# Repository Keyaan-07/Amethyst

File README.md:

# Amethyst
Amethyst is an 84-key keyboard with a small form factor. It comes with the RP2040 and i have used purple akko v3 switches to give it purple colour. This keyboard runs qmk firmware and can be found under firmware. The complete design file is amethyst.step.

# Soldering and setup
1. Order the PCB from the gerbers present in hardware/production. 
2. order the parts from the given links in bom.csv file
3. first solder the smd components on the back side and then proceed to the through hole keys. 
4. press the heated inserts in the case with the help of a soldering iron. 
5. screw in the case. 
6. fit the keycaps on the top. 
7. short the BOOT and GND pads with a screwdriver and plug in the usb cable.
8. go to the firmware folder and download the .uf2 file. 
9. drag and drop the .uf2 file to the "RPI-RP2" drive that just popped up.
10. Your keyboard is now ready!!

## Why I made this keyboard
 I am getting a new laptop this year and did not want to let go of the keymap of the old keyboard, thus I created amethyst. 

# BOM
|Designator                                                                                                                                                                                                                                                                                                                                                                                                               |Function                      |Value                      |Footprint                            |Quantity|Price   |Amount |Order|Link                                                                                                                                     |
|-------------------------------------------------------------------------------------------------------------------------------------------------------------------------------------------------------------------------------------------------------------------------------------------------------------------------------------------------------------------------------------------------------------------------|------------------------------|---------------------------|-------------------------------------|--------|--------|-------|-----|-----------------------------------------------------------------------------------------------------------------------------------------|
|PCB                                                                                                                                                                                                                                                                                                                                                                                                                      |Main PCB                      |                           |119x312                              |5       |8.934   |44.67  |Yes  |https://robu.in/product/online-pcb-manufacturing-service/                                                                                |
|Keycaps                                                                                                                                                                                                                                                                                                                                                                                                                  |Purple keycaps                |                           |                                     |1       |11.48   |11.48  |Yes  |https://curiositycaps.in/products/macarons-cherry-pbt-keycaps?_pos=368&_fid=c796727f4&_ss=c                                              |
|Keys                                                                                                                                                                                                                                                                                                                                                                                                                     |Akko v3 lavender(pack of 45)  |                           |                                     |2       |11.48   |22.96  |Yes  |https://stackskb.com/store/akko-v3-lavender-purple-pro-switch-pack-of-45/                                                                |
|Stabilizers                                                                                                                                                                                                                                                                                                                                                                                                              |Clear                         |                           |                                     |1       |11.67   |11.67  |Yes  |https://stackskb.com/store/durock-clear-screw-in-stabilizers-v2/?attribute_combination=4%2B1+Set&attribute_spacebar-size=6.25U           |
|Case                                                                                                                                                                                                                                                                                                                                                                                                                     |print legion                  |                           |                                     |1       |0       |0      |Yes  |https://printlegion.hackclub.com/                                                                                                        |
|C1, C2                                                                                                                                                                                                                                                                                                                                                                                                                   |Capacitor                     |15p                        |402                                  |2       |0.017   |0.034  |Yes  |https://robu.in/product/gjm1555c1h150gb01d-murata-electronics-50v-15pf-null-%c2%b12-0402-multilayer-ceramic-capacitors-mlcc-smd-smt-rohs/|
|C13, C22                                                                                                                                                                                                                                                                                                                                                                                                                 |Capacitor                     |10u                        |805                                  |2       |0.05    |0.1    |No   |https://www.lcsc.com/product-detail/C2932476.html                                                                                        |
|C14, C15, C16, C17, C18, C19, C20, C23, C24, C25                                                                                                                                                                                                                                                                                                                                                                         |Capacitor                     |100n                       |402                                  |10      |0.0074  |0.074  |No   |https://www.lcsc.com/product-detail/C426067.html                                                                                         |
|C4, C5, C6                                                                                                                                                                                                                                                                                                                                                                                                               |Capacitor                     |1u                         |402                                  |3       |0.02    |0.06   |No   |https://www.lcsc.com/product-detail/C1518208.html                                                                                        |
|D1, D10, D11, D12, D13, D14, D15, D16, D17, D18, D19, D2, D20, D21, D22, D23, D24, D25, D26, D27, D28, D29, D3, D30, D31, D32, D33, D34, D35, D36, D37, D38, D39, D4, D40, D41, D42, D43, D44, D45, D46, D47, D48, D49, D5, D50, D51, D52, D53, D54, D55, D56, D57, D58, D59, D6, D60, D61, D62, D63, D64, D65, D66, D67, D68, D69, D7, D70, D71, D72, D73, D74, D75, D76, D77, D78, D79, D8, D80, D81, D82, D83, D84, D9|Diodes                        |1N4148W                    |D_SOD-123                            |90      |0.0073  |0.657  |Yes  |https://robu.in/product/1n4148w-sod-123-1206-diodereel-of-3000/                                                                          |
|J2                                                                                                                                                                                                                                                                                                                                                                                                                       |USB-C                         |USB_C_Receptacle_USB2.0_16P|USB_C_Receptacle_XKB_U262-16XN-4BVC11|1       |0.06    |0.06   |No   |https://www.lcsc.com/product-detail/C393939.html                                                                                         |
|R1, R2                                                                                                                                                                                                                                                                                                                                                                                                                   |Resistors                     |5.1k                       |402                                  |2       |0.005   |0.01   |No   |https://www.lcsc.com/product-detail/C278598.html                                                                                         |
|R3, R6                                                                                                                                                                                                                                                                                                                                                                                                                   |Resistors                     |1k                         |402                                  |2       |0.02    |0.04   |No   |https://www.lcsc.com/product-detail/C427241.html                                                                                         |
|R4, R5                                                                                                                                                                                                                                                                                                                                                                                                                   |Resistors                     |27                         |402                                  |2       |0.0039  |0.0078 |No   |https://www.lcsc.com/product-detail/C278580.html                                                                                         |
|U1                                                                                                                                                                                                                                                                                                                                                                                                                       |MCU                           |RP2040                     |QFN-56-1EP_7x7mm_P0.4mm_EP3.2x3.2mm  |2       |0.89    |1.78   |Yes  |https://robu.in/product/raspberry-pi-rp2040/                                                                                             |
|U2                                                                                                                                                                                                                                                                                                                                                                                                                       |Flash                         |W25Q128JVS                 |SOIC-8_5.3x5.3mm_P1.27mm             |1       |1.1     |1.1    |No   |https://www.lcsc.com/product-detail/C2613930.html                                                                                        |
|U3                                                                                                                                                                                                                                                                                                                                                                                                                       |Regulator                     |AMS1117-3.3                |SOT-89-3                             |1       |0.1     |0.1    |No   |https://www.lcsc.com/product-detail/C917152.html                                                                                         |
|Y1                                                                                                                                                                                                                                                                                                                                                                                                                       |Crystal Oscillator            |Crystal_GND24              |Crystal_SMD_3225-4Pin_3.2x2.5mm      |1       |0.38    |0.38   |No   |https://www.lcsc.com/product-detail/C20625731.html                                                                                       |
|                                                                                                                                                                                                                                                                                                                                                                                                                         |                              |                           |                                     |        |Shipping|0.51   |     |                                                                                                                                         |
|                                                                                                                                                                                                                                                                                                                                                                                                                         |                              |                           |                                     |        |Total   |100.693|     |                                                                                                                                         |

# 3d Files link
All the 3d files can be found on onshape [here](https://cad.onshape.com/documents/0f11901139fd6ce9006e5c5f/w/93aac7747a7c2381c6948375/e/141b0f824d8e79d984ecb6aa?renderMode=0&uiState=6a158fa1dd36a79bc530a0cf)

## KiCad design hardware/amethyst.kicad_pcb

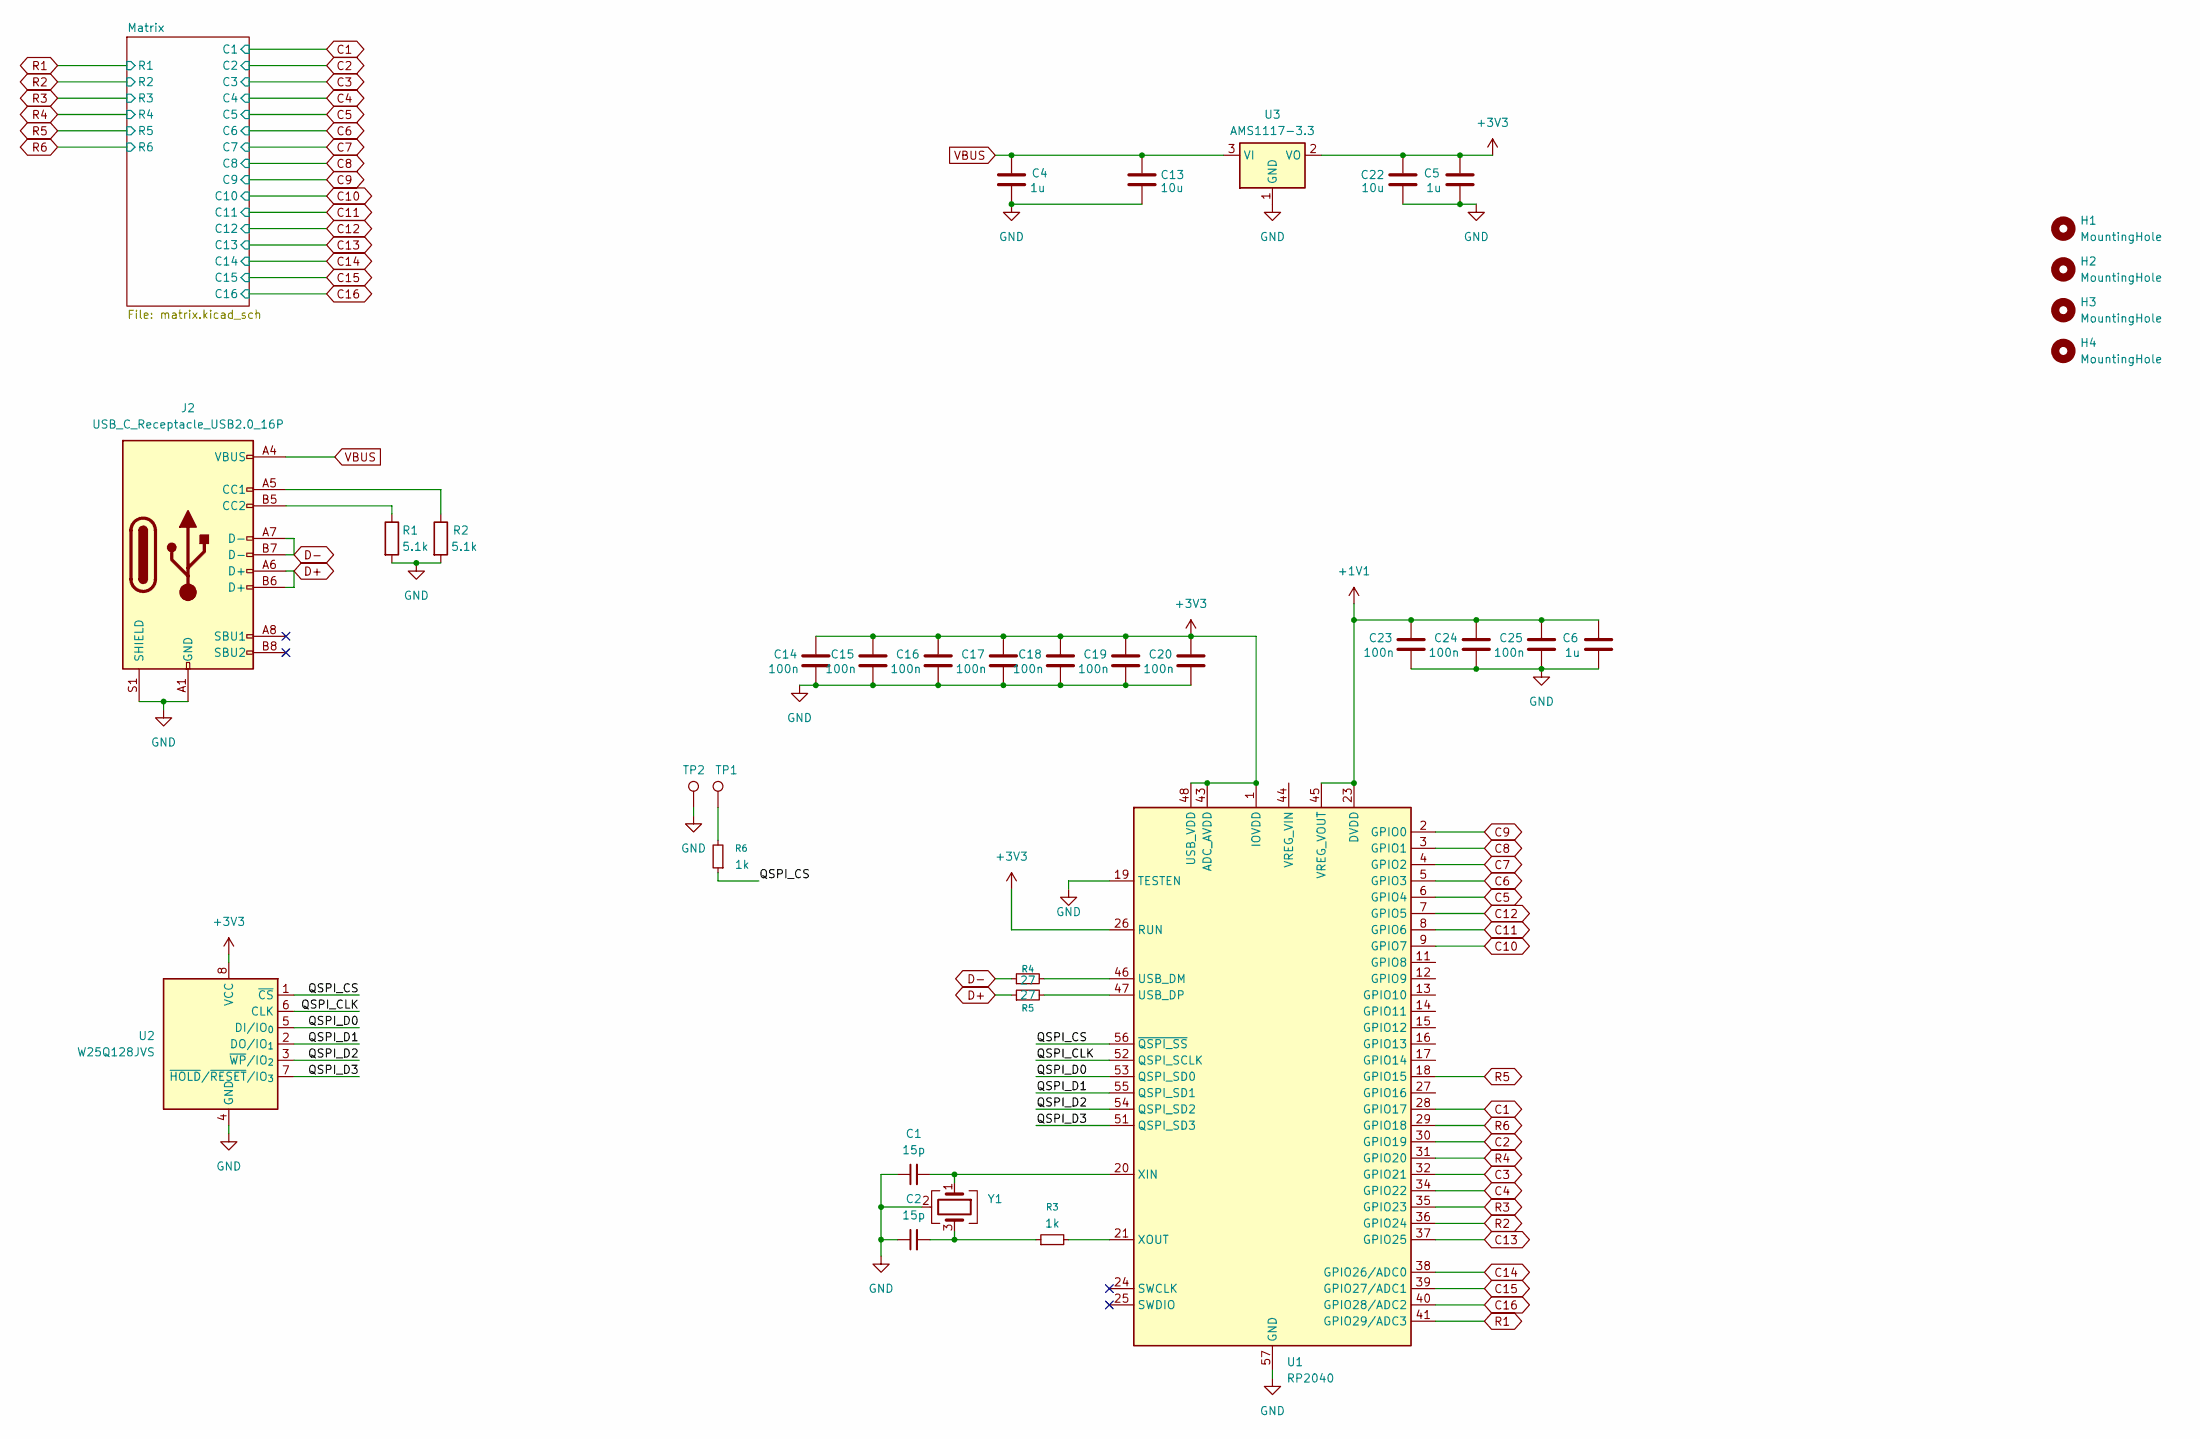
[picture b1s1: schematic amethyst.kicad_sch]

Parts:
C1, C2: 15p; C_0402_1005Metric
C4, C5, C6: 1u; C_0402_1005Metric
C13, C22: 10u; C_0805_2012Metric
C14, C15, C16, C17, C18, C19, C20, C23, C24, C25: 100n; C_0402_1005Metric
H1, H2, H3, H4: MountingHole; MountingHole_3.2mm_M3
J2: USB_C_Receptacle_USB2.0_16P; USB_C_Receptacle_XKB_U262-16XN-4BVC11
R1, R2: 5.1k; R_0402_1005Metric
R3, R6: 1k; R_0402_1005Metric
R4, R5: 27; R_0402_1005Metric
TP1, TP2: TestPoint; TestPoint_Pad_1.0x1.0mm
U1: RP2040; QFN-56-1EP_7x7mm_P0.4mm_EP3.2x3.2mm
U2: W25Q128JVS; SOIC-8_5.3x5.3mm_P1.27mm
U3: AMS1117-3.3; SOT-89-3
Y1: Crystal_GND24; Crystal_SMD_3225-4Pin_3.2x2.5mm

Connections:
+1V1: C6.2, C23.2, C24.2, C25.2, U1.23 (DVDD), U1.45 (VREG_VOUT), U1.50 (DVDD)
+3V3: C5.2, C14.2, C15.2, C16.2, C17.2, C18.2, C19.2, C20.2, C22.1, U1.1 (IOVDD), U1.10 (IOVDD), U1.22 (IOVDD), U1.26 (RUN), U1.33 (IOVDD), U1.42 (IOVDD), U1.43 (ADC_AVDD), U1.48 (USB_VDD), U1.49 (IOVDD), U2.8 (VCC), U3.2 (VO)
/QSPI_CLK: U1.52 (QSPI_SCLK), U2.6 (CLK)
/QSPI_CS: R6.1, U1.56 (~QSPI_SS), U2.1 (~CS)
/QSPI_D0: U1.53 (QSPI_SD0), U2.5 (DI/IO_{0})
/QSPI_D1: U1.55 (QSPI_SD1), U2.2 (DO/IO_{1})
/QSPI_D2: U1.54 (QSPI_SD2), U2.3 (~WP/IO_{2})
/QSPI_D3: U1.51 (QSPI_SD3), U2.7 (~HOLD/~RESET/IO_{3})
C1: U1.28 (GPIO17); also elsewhere on the board
C2: U1.30 (GPIO19); also elsewhere on the board
C3: U1.32 (GPIO21); also elsewhere on the board
C4: U1.34 (GPIO22); also elsewhere on the board
C5: U1.6 (GPIO4); also elsewhere on the board
C6: U1.5 (GPIO3); also elsewhere on the board
C7: U1.4 (GPIO2); also elsewhere on the board
C8: U1.3 (GPIO1); also elsewhere on the board
C9: U1.2 (GPIO0); also elsewhere on the board
C10: U1.9 (GPIO7); also elsewhere on the board
C11: U1.8 (GPIO6); also elsewhere on the board
C12: U1.7 (GPIO5); also elsewhere on the board
C13: U1.37 (GPIO25); also elsewhere on the board
C14: U1.38 (GPIO26/ADC0); also elsewhere on the board
C15: U1.39 (GPIO27/ADC1); also elsewhere on the board
C16: U1.40 (GPIO28/ADC2); also elsewhere on the board
D+: J2.A6 (D+), J2.B6 (D+), R5.1
D-: J2.A7 (D-), J2.B7 (D-), R4.1
GND: C1.1, C2.1, C4.1, C5.1, C6.1, C13.2, C14.1, C15.1, C16.1, C17.1, C18.1, C19.1, C20.1, C22.2, C23.1, C24.1, C25.1, J2.A1 (GND), J2.A12 (GND), J2.B1 (GND), J2.B12 (GND), J2.S1 (SHIELD), R1.2, R2.2, TP2.1 (1_1), U1.19 (TESTEN), U1.57 (GND), U2.4 (GND), U3.1 (GND), Y1.2 (G), Y1.4 (G)
unnamed: C2.2, R3.1, Y1.3
unnamed: J2.A5 (CC1), R2.1
unnamed: J2.B5 (CC2), R1.1
unnamed: R6.2, TP1.1 (1_1)
unnamed: R4.2, U1.46 (USB_DM)
unnamed: R5.2, U1.47 (USB_DP)
unnamed: C1.2, U1.20 (XIN), Y1.1
unnamed: R3.2, U1.21 (XOUT)
R1: U1.41 (GPIO29/ADC3); also elsewhere on the board
R2: U1.36 (GPIO24); also elsewhere on the board
R3: U1.35 (GPIO23); also elsewhere on the board
R4: U1.31 (GPIO20); also elsewhere on the board
R5: U1.18 (GPIO15); also elsewhere on the board
R6: U1.29 (GPIO18); also elsewhere on the board
VBUS: C4.2, C13.1, J2.A4 (VBUS), J2.A9 (VBUS), J2.B4 (VBUS), J2.B9 (VBUS), U3.3 (VI)

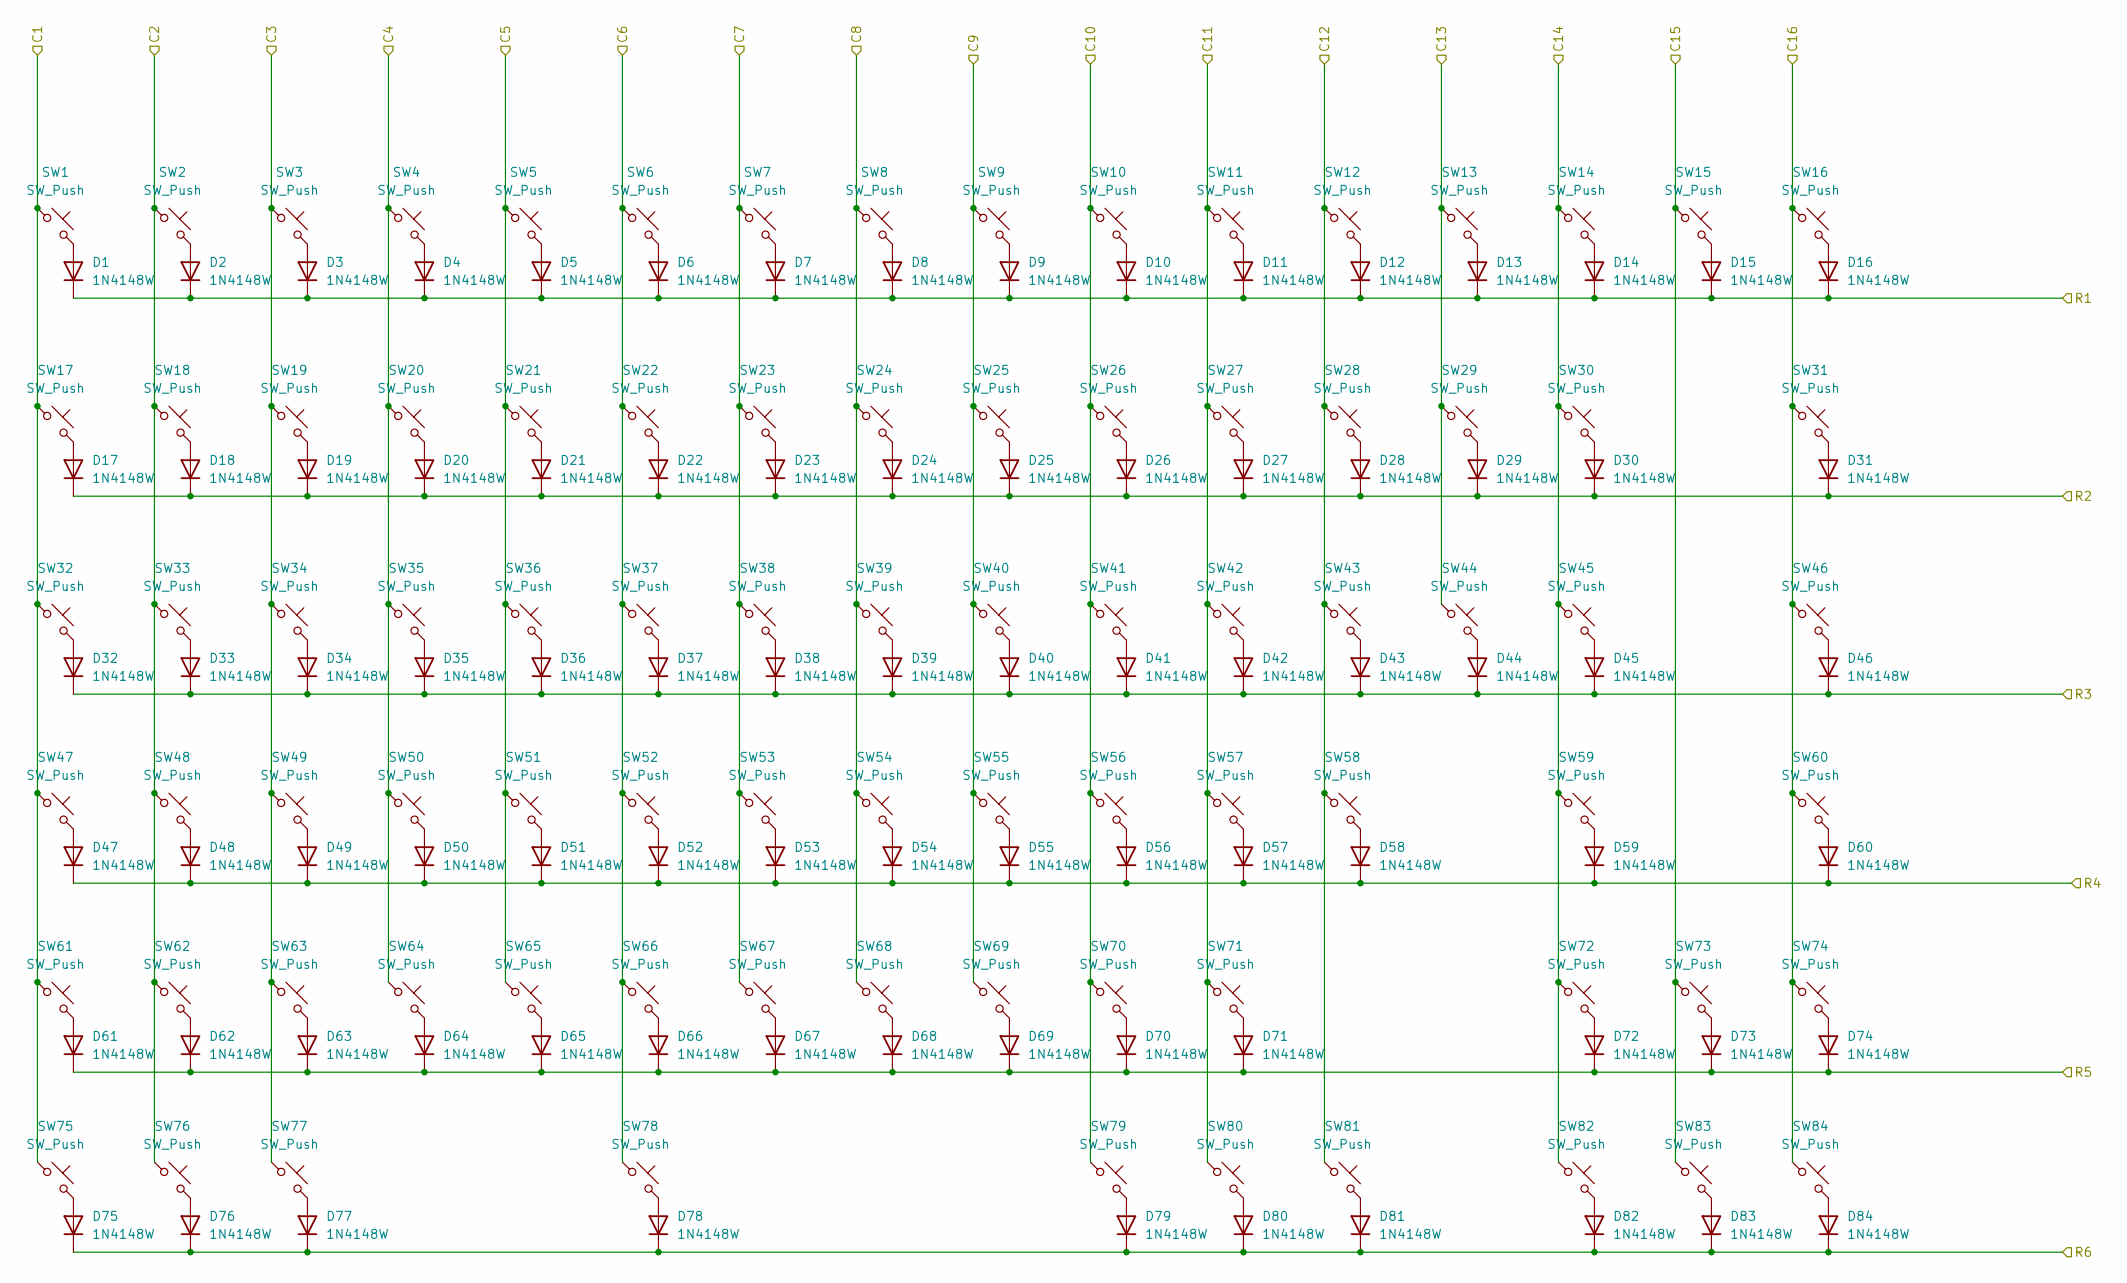
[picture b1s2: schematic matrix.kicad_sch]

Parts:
D1, D2, D3, D4, D5, D6, D7, D8, D9, D10, D11, D12, D13, D14, D15, D16, D17, D18, D19, D20, D21, D22, D23, D24, D25, D26, D27, D28, D29, D30, D31, D32, D33, D34, D35, D36, D37, D38, D39, D40, D41, D42, D43, D44, D45, D46, D47, D48, D49, D50, D51, D52, D53, D54, D55, D56, D57, D58, D59, D60, D61, D62, D63, D64, D65, D66, D67, D68, D69, D70, D71, D72, D73, D74, D75, D76, D77, D78, D79, D80, D81, D82, D83, D84: 1N4148W; D_SOD-123
SW1, SW2, SW3, SW4, SW5, SW6, SW7, SW8, SW9, SW10, SW11, SW12, SW13, SW14, SW15, SW16, SW17, SW18, SW19, SW20, SW21, SW22, SW23, SW24, SW25, SW26, SW27, SW28, SW29, SW31, SW33, SW34, SW35, SW36, SW37, SW38, SW39, SW40, SW41, SW42, SW43, SW44, SW46, SW48, SW49, SW50, SW51, SW52, SW53, SW54, SW55, SW56, SW57, SW58, SW60, SW62, SW63, SW64, SW65, SW66, SW67, SW68, SW69, SW70, SW71, SW73, SW74, SW79, SW80, SW81, SW82, SW83, SW84: SW_Push; SW_Cherry_MX_1.00u_PCB
SW30: SW_Push; SW_Cherry_MX_2.00u_PCB
SW32, SW45: SW_Push; SW_Cherry_MX_1.50u_PCB
SW47, SW72: SW_Push; SW_Cherry_MX_1.75u_PCB
SW59, SW61: SW_Push; SW_Cherry_MX_2.25u_PCB
SW75, SW76, SW77: SW_Push; SW_Cherry_MX_1.25u_PCB
SW78: SW_Push; SW_Cherry_MX_6.25u_PCB

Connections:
C1: SW1.1, SW17.1, SW32.1, SW47.1, SW61.1, SW75.1; also elsewhere on the board
C2: SW2.1, SW18.1, SW33.1, SW48.1, SW62.1, SW76.1; also elsewhere on the board
C3: SW3.1, SW19.1, SW34.1, SW49.1, SW63.1, SW77.1; also elsewhere on the board
C4: SW4.1, SW20.1, SW35.1, SW50.1, SW64.1; also elsewhere on the board
C5: SW5.1, SW21.1, SW36.1, SW51.1, SW65.1; also elsewhere on the board
C6: SW6.1, SW22.1, SW37.1, SW52.1, SW66.1, SW78.1; also elsewhere on the board
C7: SW7.1, SW23.1, SW38.1, SW53.1, SW67.1; also elsewhere on the board
C8: SW8.1, SW24.1, SW39.1, SW54.1, SW68.1; also elsewhere on the board
C9: SW9.1, SW25.1, SW40.1, SW55.1, SW69.1; also elsewhere on the board
C10: SW10.1, SW26.1, SW41.1, SW56.1, SW70.1, SW79.1; also elsewhere on the board
C11: SW11.1, SW27.1, SW42.1, SW57.1, SW71.1, SW80.1; also elsewhere on the board
C12: SW12.1, SW28.1, SW43.1, SW58.1, SW81.1; also elsewhere on the board
C13: SW13.1, SW29.1, SW44.1; also elsewhere on the board
C14: SW14.1, SW30.1, SW45.1, SW59.1, SW72.1, SW82.1; also elsewhere on the board
C15: SW15.1, SW73.1, SW83.1; also elsewhere on the board
C16: SW16.1, SW31.1, SW46.1, SW60.1, SW74.1, SW84.1; also elsewhere on the board
unnamed: D1.2 (A), SW1.2
unnamed: D2.2 (A), SW2.2
unnamed: D3.2 (A), SW3.2
unnamed: D4.2 (A), SW4.2
unnamed: D5.2 (A), SW5.2
unnamed: D6.2 (A), SW6.2
unnamed: D7.2 (A), SW7.2
unnamed: D8.2 (A), SW8.2
unnamed: D9.2 (A), SW9.2
unnamed: D10.2 (A), SW10.2
unnamed: D11.2 (A), SW11.2
unnamed: D12.2 (A), SW12.2
unnamed: D13.2 (A), SW13.2
unnamed: D14.2 (A), SW14.2
unnamed: D15.2 (A), SW15.2
unnamed: D16.2 (A), SW16.2
unnamed: D17.2 (A), SW17.2
unnamed: D18.2 (A), SW18.2
unnamed: D19.2 (A), SW19.2
unnamed: D20.2 (A), SW20.2
unnamed: D21.2 (A), SW21.2
unnamed: D22.2 (A), SW22.2
unnamed: D23.2 (A), SW23.2
unnamed: D24.2 (A), SW24.2
unnamed: D25.2 (A), SW25.2
unnamed: D26.2 (A), SW26.2
unnamed: D27.2 (A), SW27.2
unnamed: D28.2 (A), SW28.2
unnamed: D29.2 (A), SW29.2
unnamed: D30.2 (A), SW30.2
unnamed: D31.2 (A), SW31.2
unnamed: D32.2 (A), SW32.2
unnamed: D33.2 (A), SW33.2
unnamed: D34.2 (A), SW34.2
unnamed: D35.2 (A), SW35.2
unnamed: D36.2 (A), SW36.2
unnamed: D37.2 (A), SW37.2
unnamed: D38.2 (A), SW38.2
unnamed: D39.2 (A), SW39.2
unnamed: D40.2 (A), SW40.2
unnamed: D41.2 (A), SW41.2
unnamed: D42.2 (A), SW42.2
unnamed: D43.2 (A), SW43.2
unnamed: D44.2 (A), SW44.2
unnamed: D45.2 (A), SW45.2
unnamed: D46.2 (A), SW46.2
unnamed: D47.2 (A), SW47.2
unnamed: D48.2 (A), SW48.2
unnamed: D49.2 (A), SW49.2
unnamed: D50.2 (A), SW50.2
unnamed: D51.2 (A), SW51.2
unnamed: D52.2 (A), SW52.2
unnamed: D53.2 (A), SW53.2
unnamed: D54.2 (A), SW54.2
unnamed: D55.2 (A), SW55.2
unnamed: D56.2 (A), SW56.2
unnamed: D57.2 (A), SW57.2
unnamed: D58.2 (A), SW58.2
unnamed: D59.2 (A), SW59.2
unnamed: D60.2 (A), SW60.2
unnamed: D61.2 (A), SW61.2
unnamed: D62.2 (A), SW62.2
unnamed: D63.2 (A), SW63.2
unnamed: D64.2 (A), SW64.2
unnamed: D65.2 (A), SW65.2
unnamed: D66.2 (A), SW66.2
unnamed: D67.2 (A), SW67.2
unnamed: D68.2 (A), SW68.2
unnamed: D69.2 (A), SW69.2
unnamed: D70.2 (A), SW70.2
unnamed: D71.2 (A), SW71.2
unnamed: D72.2 (A), SW72.2
unnamed: D73.2 (A), SW73.2
unnamed: D74.2 (A), SW74.2
unnamed: D75.2 (A), SW75.2
unnamed: D76.2 (A), SW76.2
unnamed: D77.2 (A), SW77.2
unnamed: D78.2 (A), SW78.2
unnamed: D79.2 (A), SW79.2
unnamed: D80.2 (A), SW80.2
unnamed: D81.2 (A), SW81.2
unnamed: D82.2 (A), SW82.2
unnamed: D83.2 (A), SW83.2
unnamed: D84.2 (A), SW84.2
R1: D1.1 (K), D2.1 (K), D3.1 (K), D4.1 (K), D5.1 (K), D6.1 (K), D7.1 (K), D8.1 (K), D9.1 (K), D10.1 (K), D11.1 (K), D12.1 (K), D13.1 (K), D14.1 (K), D15.1 (K), D16.1 (K); also elsewhere on the board
R2: D17.1 (K), D18.1 (K), D19.1 (K), D20.1 (K), D21.1 (K), D22.1 (K), D23.1 (K), D24.1 (K), D25.1 (K), D26.1 (K), D27.1 (K), D28.1 (K), D29.1 (K), D30.1 (K), D31.1 (K); also elsewhere on the board
R3: D32.1 (K), D33.1 (K), D34.1 (K), D35.1 (K), D36.1 (K), D37.1 (K), D38.1 (K), D39.1 (K), D40.1 (K), D41.1 (K), D42.1 (K), D43.1 (K), D44.1 (K), D45.1 (K), D46.1 (K); also elsewhere on the board
R4: D47.1 (K), D48.1 (K), D49.1 (K), D50.1 (K), D51.1 (K), D52.1 (K), D53.1 (K), D54.1 (K), D55.1 (K), D56.1 (K), D57.1 (K), D58.1 (K), D59.1 (K), D60.1 (K); also elsewhere on the board
R5: D61.1 (K), D62.1 (K), D63.1 (K), D64.1 (K), D65.1 (K), D66.1 (K), D67.1 (K), D68.1 (K), D69.1 (K), D70.1 (K), D71.1 (K), D72.1 (K), D73.1 (K), D74.1 (K); also elsewhere on the board
R6: D75.1 (K), D76.1 (K), D77.1 (K), D78.1 (K), D79.1 (K), D80.1 (K), D81.1 (K), D82.1 (K), D83.1 (K), D84.1 (K); also elsewhere on the board

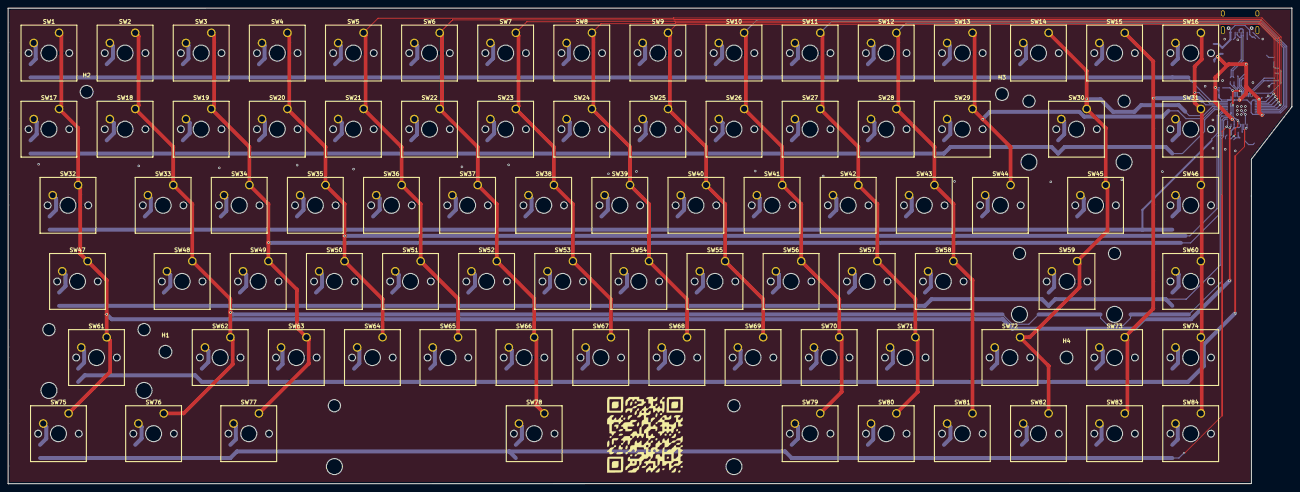
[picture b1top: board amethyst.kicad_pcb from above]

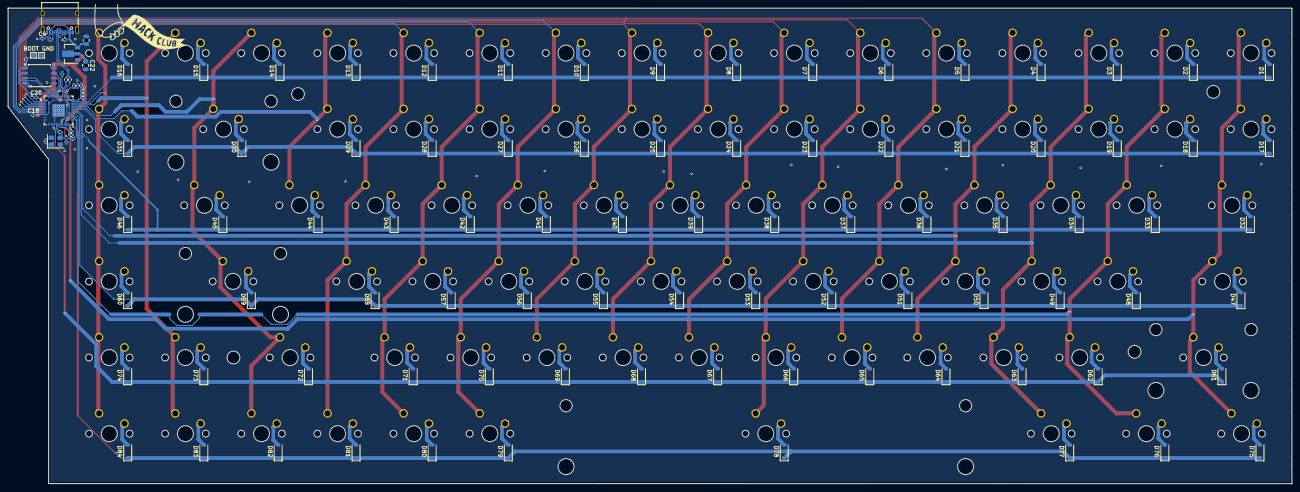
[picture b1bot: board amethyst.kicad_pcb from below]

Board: 2 copper layers, 321.3 x 119.0 mm, 202 parts (114 on the bottom side), 126 nets.

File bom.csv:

Designator,Function,Value,Footprint,Quantity,Price,Amount,Order,Link
PCB,Main PCB,,119x312,5,8.934,44.67,Yes,https://robu.in/product/online-pcb-manufacturing-service/
Keycaps,Purple keycaps,,,1,11.48,11.48,Yes,https://curiositycaps.in/products/macarons-cherry-pbt-keycap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
Keys,Akko v3 lavender (Pack of 45),,,2,11.48,22.96,Yes,https://stackskb.com/store/akko-v3-lavender-purple-pro-switc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
Stabilizers,Clear,,,1,16.67,16.67,Yes,https://stackskb.com/store/durock-clear-screw-in-stabilizers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
Case,print legion,,,1,0,0,Yes,https://printlegion.hackclub.com/
"C1, C2",Capacitor,15p,402,2,0.017,0.034,Yes,https://robu.in/product/gjm1555c1h150gb01d-murata-electronic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
"C13, C22",Capacitor,10u,805,2,0.05,0.1,No,https://www.lcsc.com/product-detail/C2932476.html
"C14, C15, C16, C17, C18, C19, C20, C23, C24, C25",Capacitor,100n,402,10,0.0074,0.074,No,https://www.lcsc.com/product-detail/C426067.html
"C4, C5, C6",Capacitor,1u,402,3,0.02,0.06,No,https://www.lcsc.com/product-detail/C1518208.html
"D1, D10, D11, D12, D13, D14, D15, D16, D17, D18, D19, D2, D20, D21, D22, D23, D24, D25, D26, D27, D28, D29, D3, D30, D31, D32, D33, D34, D35, D36, D37, D38, D39, D4, D40, D41, D42, D43, D44, D45, D46, D47, D48, D49, D5, D50, D51, D52, D53, D54, D55, D56, D57, D58, D59, D6, D60, D61, D62, D63, D64, D65, D66, D67, D68, D69, D7, D70, D71, D72, D73, D74, D75, D76, D77, D78, D79, D8, D80, D81, D82, D83, D84, D9",Diodes,1N4148W,D_SOD-123,90,0.0073,0.657,Yes,https://robu.in/product/1n4148w-sod-123-1206-diodereel-of-3000/
J2,USB-C,USB_C_Receptacle_USB2.0_16P,USB_C_Receptacle_XKB_U262-16XN-4BVC11,1,0.06,0.06,No,https://www.lcsc.com/product-detail/C393939.html
"R1, R2",Resistors,5.1k,402,2,0.005,0.01,No,https://www.lcsc.com/product-detail/C278598.html
"R3, R6",Resistors,1k,402,2,0.02,0.04,No,https://www.lcsc.com/product-detail/C427241.html
"R4, R5",Resistors,27,402,2,0.0039,0.0078,No,https://www.lcsc.com/product-detail/C278580.html
U1,MCU,RP2040,QFN-56-1EP_7x7mm_P0.4mm_EP3.2x3.2mm,2,0.89,1.78,Yes,https://robu.in/product/raspberry-pi-rp2040/
U2,Flash,W25Q128JVS,SOIC-8_5.3x5.3mm_P1.27mm,1,1.1,1.1,No,https://www.lcsc.com/product-detail/C2613930.html
U3,Regulator,AMS1117-3.3,SOT-89-3,1,0.1,0.1,No,https://www.lcsc.com/product-detail/C917152.html
Y1,Crystal Oscillator,Crystal_GND24,Crystal_SMD_3225-4Pin_3.2x2.5mm,1,0.38,0.38,No,https://www.lcsc.com/product-detail/C20625731.html
,,,,,Shipping,0.51,,
,,,,,Total,100.6928,,

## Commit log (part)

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2026-04-29 Matrix Complete
2026-04-29 Layout done
2026-04-30 Backups
2026-04-30 Added README
2026-04-30 PCB Routing
2026-05-01 Power circuitry and nrf52840 circuitry
2026-05-02 Routing
2026-05-03 Matrix Routing and antenna placement
2026-05-03 matrix routing
2026-05-04 Routing complete
2026-05-05 Antenna matching done
2026-05-08 Prod files
2026-05-16 new MCU
2026-05-17 PCB redone
2026-05-17 new 3D model
2026-05-23 Images
2026-05-23 QMK yay
2026-05-23 all the three dimensional files
2026-05-23 New iamge
2026-05-23 Updated it, yes
2026-05-23 Onshape link
2026-05-24 Schematic Image
2026-05-24 PCB 3d model
2026-05-24 Latest Production files
2026-05-24 updated BOM
2026-05-24 updated BOM in the readme
2026-05-24 new designs
2026-05-26 new PCB design file
2026-05-26 New link
2026-05-26 new images
2026-05-26 prod
2026-05-26 reason
2026-05-26 zine page added
2026-05-26 render for images
2026-05-26 add description for key caps
2026-05-26 Updated hole height in the case
2026-05-26 removed backup files
2026-06-03 updated files for 3d models
2026-06-03 pcb completed.
2026-06-04 final production files!
2026-06-28 latest prod files
